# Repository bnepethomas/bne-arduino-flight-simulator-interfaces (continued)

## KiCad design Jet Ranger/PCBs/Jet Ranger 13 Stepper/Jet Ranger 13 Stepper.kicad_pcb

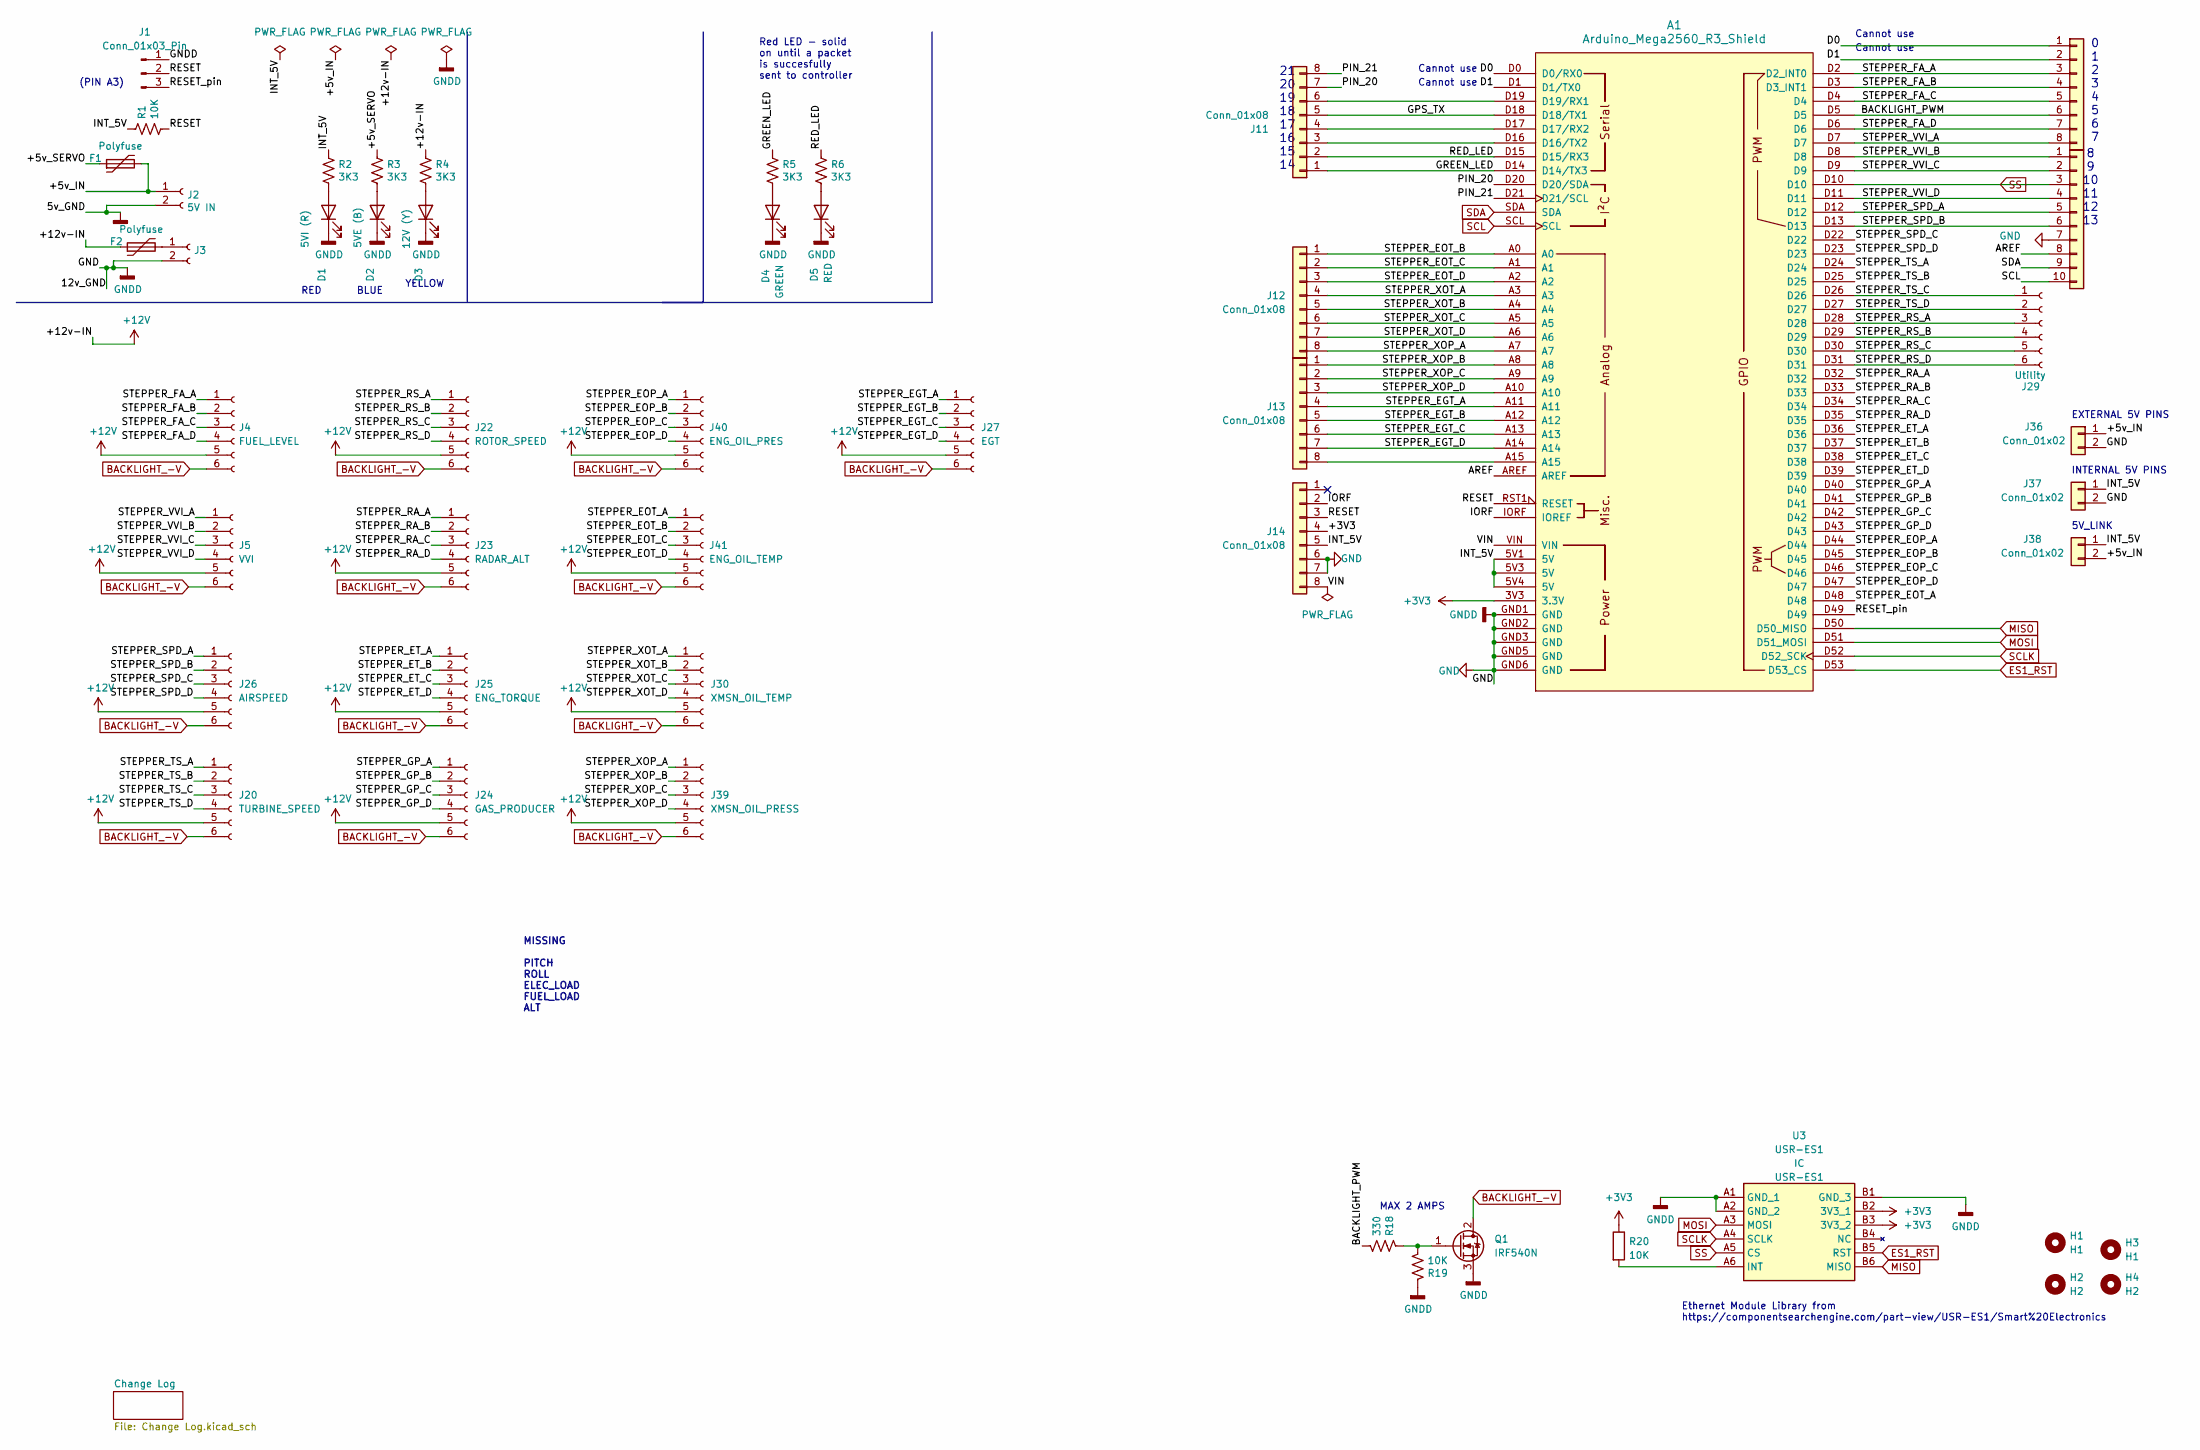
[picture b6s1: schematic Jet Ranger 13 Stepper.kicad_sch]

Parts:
A1: Arduino_Mega2560_R3_Shield
D1: 5VI (R); LED_D3.0mm
D2: 5VE (B); LED_D3.0mm
D3: 12V (Y); LED_D3.0mm
D4: GREEN; LED_D3.0mm
D5: RED; LED_D3.0mm
F1, F2: Polyfuse; Fuse_Littelfuse_395Series
H1, H3: H1; MountingHole_3.2mm_M3
H2, H4: H2; MountingHole_3.2mm_M3
J1: Conn_01x03_Pin; PinHeader_1x03_P2.54mm_Vertical
J2: 5V IN; BarrelJack_Horizontal
J3: STEPPER IN 12-20VDC; BarrelJack_Horizontal
J4: FUEL_LEVEL; Molex_KK-254_AE-6410-06A_1x06_P2.54mm_Vertical
J5: VVI; Molex_KK-254_AE-6410-06A_1x06_P2.54mm_Vertical
J11, J12, J13, J14, J34: Conn_01x08; PinHeader_1x08_P2.54mm_Vertical
J20: TURBINE_SPEED; Molex_KK-254_AE-6410-06A_1x06_P2.54mm_Vertical
J22: ROTOR_SPEED; Molex_KK-254_AE-6410-06A_1x06_P2.54mm_Vertical
J23: RADAR_ALT; Molex_KK-254_AE-6410-06A_1x06_P2.54mm_Vertical
J24: GAS_PRODUCER; Molex_KK-254_AE-6410-06A_1x06_P2.54mm_Vertical
J25: ENG_TORQUE; Molex_KK-254_AE-6410-06A_1x06_P2.54mm_Vertical
J26: AIRSPEED; Molex_KK-254_AE-6410-06A_1x06_P2.54mm_Vertical
J27: EGT; Molex_KK-254_AE-6410-06A_1x06_P2.54mm_Vertical
J29: Utility; PinHeader_1x06_P2.54mm_Vertical
J30: XMSN_OIL_TEMP; Molex_KK-254_AE-6410-06A_1x06_P2.54mm_Vertical
J35: Conn_01x10; PinHeader_1x10_P2.54mm_Vertical
J36, J37, J38: Conn_01x02; PinHeader_1x02_P2.54mm_Vertical
J39: XMSN_OIL_PRESS; Molex_KK-254_AE-6410-06A_1x06_P2.54mm_Vertical
J40: ENG_OIL_PRES; Molex_KK-254_AE-6410-06A_1x06_P2.54mm_Vertical
J41: ENG_OIL_TEMP; Molex_KK-254_AE-6410-06A_1x06_P2.54mm_Vertical
Q1: IRF540N; TO-220-3_Vertical
R1, R19, R20: 10K; R_Axial_DIN0207_L6.3mm_D2.5mm_P2.54mm_Vertical
R2, R3, R4, R5, R6: 3K3; R_Axial_DIN0207_L6.3mm_D2.5mm_P2.54mm_Vertical
R18: 330; R_Axial_DIN0207_L6.3mm_D2.5mm_P2.54mm_Vertical
U3: USR-ES1; USRES1; Manufacturer_Part_Number USR-ES1

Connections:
+3V3: A1.3V3 (3.3V), J14.4, R20.1, U3.B2 (3V3_1), U3.B3 (3V3_2)
+12V: F2.1, J4.5, J5.5, J20.5, J22.5, J23.5, J24.5, J25.5, J26.5, J27.5, J30.5, J39.5, J40.5, J41.5, R4.1
/+5v_IN: F1.2, J2.1, J36.1, J38.2
/+5v_SERVO: F1.1, R3.1
/AREF: A1.AREF, J35.8
/BACKLIGHT_PWM: A1.D5, J34.6, R18.2
/D0: A1.D0 (D0/RX0), J34.1
/D1: A1.D1 (D1/TX0), J34.2
/GPS_TX: A1.D18 (D18/TX1), J11.5
/GREEN_LED: A1.D14 (D14/TX3), J11.1, R5.1
/INT_5V: A1.5V1 (5V), A1.5V3 (5V), A1.5V4 (5V), J14.5, J37.1, J38.1, R1.1, R2.1
/IORF: A1.IORF (IOREF), J14.2
/PIN_20: A1.D20 (D20/SDA), J11.7
/PIN_21: A1.D21 (D21/SCL), J11.8
/RED_LED: A1.D15 (D15/RX3), J11.2, R6.1
/RESET: A1.RST1 (RESET), J1.2, J14.3, R1.2
/RESET_pin: A1.D49, J1.3
/STEPPER_EGT_A: A1.A11, J13.4, J27.1
/STEPPER_EGT_B: A1.A12, J13.5, J27.2
/STEPPER_EGT_C: A1.A13, J13.6, J27.3
/STEPPER_EGT_D: A1.A14, J13.7, J27.4
/STEPPER_EOP_A: A1.D44, J40.1
/STEPPER_EOP_B: A1.D45, J40.2
/STEPPER_EOP_C: A1.D46, J40.3
/STEPPER_EOP_D: A1.D47, J40.4
/STEPPER_EOT_A: A1.D48, J41.1
/STEPPER_EOT_B: A1.A0, J12.1, J41.2
/STEPPER_EOT_C: A1.A1, J12.2, J41.3
/STEPPER_EOT_D: A1.A2, J12.3, J41.4
/STEPPER_ET_A: A1.D36, J25.1
/STEPPER_ET_B: A1.D37, J25.2
/STEPPER_ET_C: A1.D38, J25.3
/STEPPER_ET_D: A1.D39, J25.4
/STEPPER_FA_A: A1.D2 (D2_INT0), J4.1, J34.3
/STEPPER_FA_B: A1.D3 (D3_INT1), J4.2, J34.4
/STEPPER_FA_C: A1.D4, J4.3, J34.5
/STEPPER_FA_D: A1.D6, J4.4, J34.7
/STEPPER_GP_A: A1.D40, J24.1
/STEPPER_GP_B: A1.D41, J24.2
/STEPPER_GP_C: A1.D42, J24.3
/STEPPER_GP_D: A1.D43, J24.4
/STEPPER_RA_A: A1.D32, J23.1
/STEPPER_RA_B: A1.D33, J23.2
/STEPPER_RA_C: A1.D34, J23.3
/STEPPER_RA_D: A1.D35, J23.4
/STEPPER_RS_A: A1.D28, J22.1, J29.3
/STEPPER_RS_B: A1.D29, J22.2, J29.4
/STEPPER_RS_C: A1.D30, J22.3, J29.5
/STEPPER_RS_D: A1.D31, J22.4, J29.6
/STEPPER_SPD_A: A1.D12, J26.1, J35.5
/STEPPER_SPD_B: A1.D13, J26.2, J35.6
/STEPPER_SPD_C: A1.D22, J26.3
/STEPPER_SPD_D: A1.D23, J26.4
/STEPPER_TS_A: A1.D24, J20.1
/STEPPER_TS_B: A1.D25, J20.2
/STEPPER_TS_C: A1.D26, J20.3, J29.1
/STEPPER_TS_D: A1.D27, J20.4, J29.2
/STEPPER_VVI_A: A1.D7, J5.1, J34.8
/STEPPER_VVI_B: A1.D8, J5.2, J35.1
/STEPPER_VVI_C: A1.D9, J5.3, J35.2
/STEPPER_VVI_D: A1.D11, J5.4, J35.4
/STEPPER_XOP_A: A1.A7, J12.8, J39.1
/STEPPER_XOP_B: A1.A8, J13.1, J39.2
/STEPPER_XOP_C: A1.A9, J13.2, J39.3
/STEPPER_XOP_D: A1.A10, J13.3, J39.4
/STEPPER_XOT_A: A1.A3, J12.4, J30.1
/STEPPER_XOT_B: A1.A4, J12.5, J30.2
/STEPPER_XOT_C: A1.A5, J12.6, J30.3
/STEPPER_XOT_D: A1.A6, J12.7, J30.4
/VIN: A1.VIN, J14.8
BACKLIGHT_-V: J4.6, J5.6, J20.6, J22.6, J23.6, J24.6, J25.6, J26.6, J27.6, J30.6, J39.6, J40.6, J41.6, Q1.2 (D)
ES1_RST: A1.D53 (D53_CS), U3.B5 (RST)
GND: A1.GND1 (GND), A1.GND2 (GND), A1.GND3 (GND), A1.GND5 (GND), A1.GND6 (GND), D1.1 (K), D2.1 (K), D3.1 (K), D4.1 (K), D5.1 (K), J1.1, J2.2, J3.2, J14.6, J14.7, J35.7, J36.2, J37.2, Q1.3 (S), R19.1, U3.A1 (GND_1), U3.A2 (GND_2), U3.B1 (GND_3)
MISO: A1.D50 (D50_MISO), U3.B6 (MISO)
MOSI: A1.D51 (D51_MOSI), U3.A3 (MOSI)
unnamed: A1.D16 (D16/TX2), J11.3
unnamed: A1.D17 (D17/RX2), J11.4
unnamed: A1.D19 (D19/RX1), J11.6
unnamed: D1.2 (A), R2.2
unnamed: D2.2 (A), R3.2
unnamed: D3.2 (A), R4.2
unnamed: D4.2 (A), R5.2
unnamed: D5.2 (A), R6.2
unnamed: F2.2, J3.1
unnamed: A1.A15, J13.8
unnamed: Q1.1 (G), R18.1, R19.2
unnamed: R20.2, U3.A6 (INT)
SCL: A1.SCL, J35.10
SCLK: A1.D52 (D52_SCK), U3.A4 (SCLK)
SDA: A1.SDA, J35.9
SS: A1.D10, J35.3, U3.A5 (CS)

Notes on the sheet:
YELLOW
MAX 2 AMPS
MISSING PITCH ROLL ELEC_LOAD FUEL_LOAD ALT
BLUE
INTERNAL 5V PINS
Ethernet Module Library from https://componentsearchengine.com/part-view/USR-ES1/Smart%20Electronics
Cannot use
RED
(PIN A3)
0 1 2 3 4 5 6 7
Red LED - solid on until a packet is succesfully sent to controller
5V_LINK
21 20 19 18 17 16 15 14
EXTERNAL 5V PINS
8 9 10 11 12 13

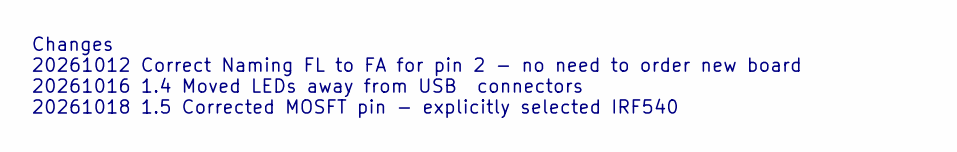
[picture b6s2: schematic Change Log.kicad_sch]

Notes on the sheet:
Changes 20261012 Correct Naming FL to FA for pin 2 - no need to order new board 20261016 1.4 Moved LEDs away from USB connectors 20261018 1.5 Corrected MOSFT pin - explicitly selected IRF540

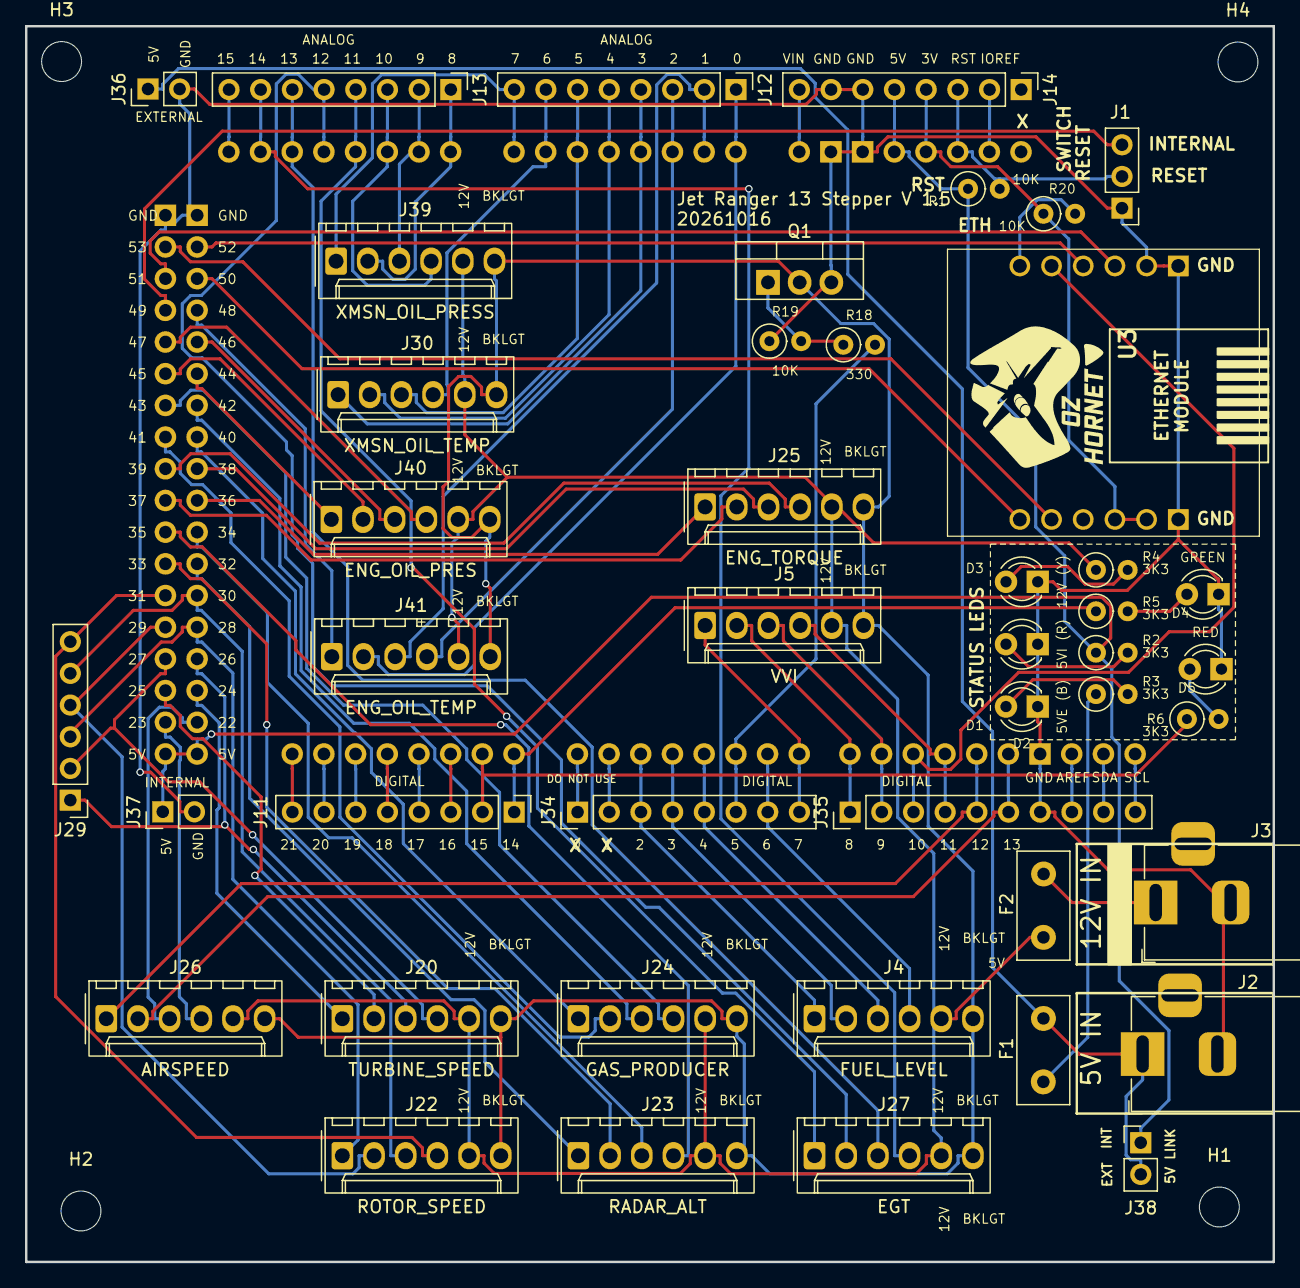
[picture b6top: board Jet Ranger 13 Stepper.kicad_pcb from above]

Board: 2 copper layers, 100.0 x 99.1 mm, 49 parts (0 on the bottom side), 91 nets.

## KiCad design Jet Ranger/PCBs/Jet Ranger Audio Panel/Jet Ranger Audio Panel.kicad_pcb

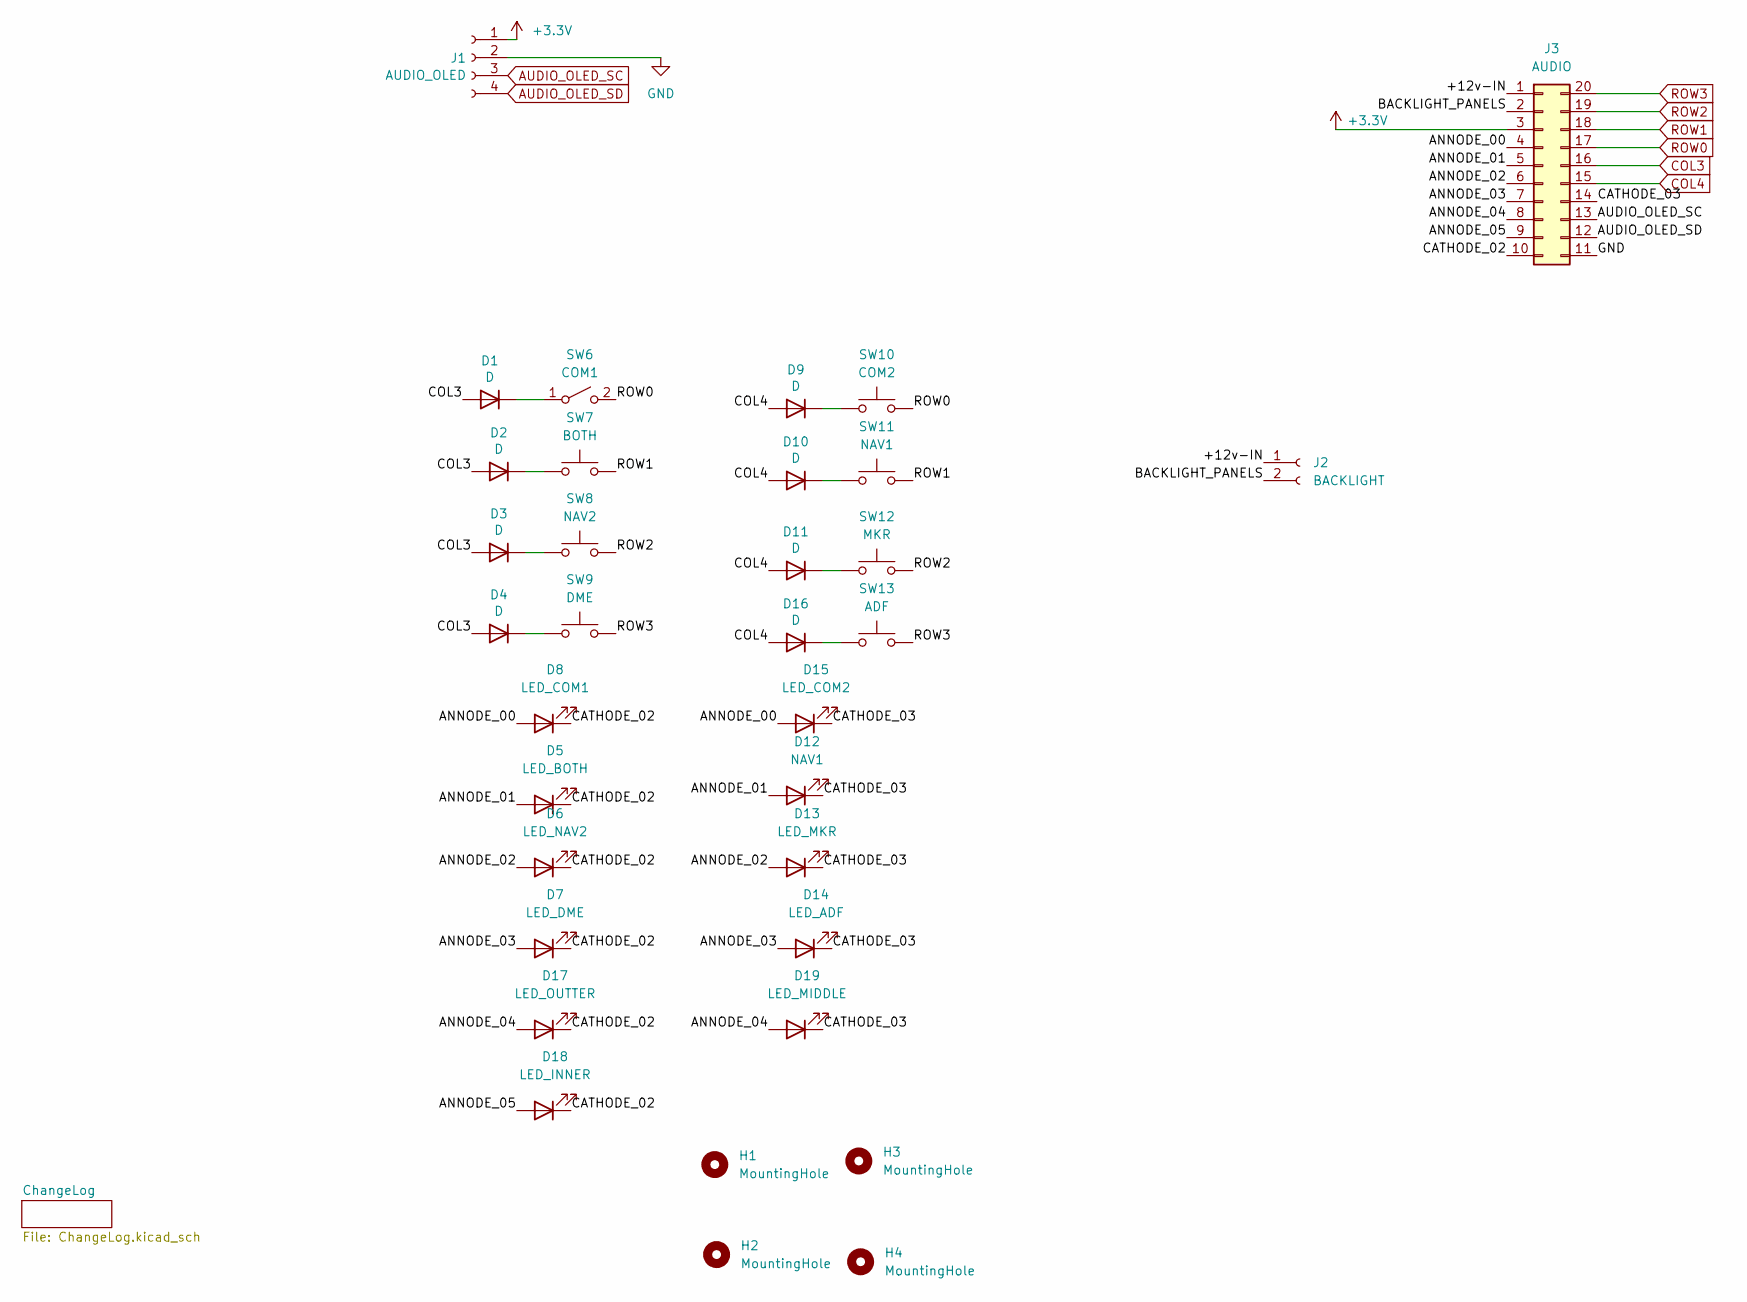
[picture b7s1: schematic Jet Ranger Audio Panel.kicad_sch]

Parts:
D1, D2, D3, D4, D9, D10, D11, D16: D; D_A-405_P7.62mm_Horizontal
D5: LED_BOTH; JST_XH_B2B-XH-A_1x02_P2.50mm_Vertical
D6: LED_NAV2; JST_XH_B2B-XH-A_1x02_P2.50mm_Vertical
D7: LED_DME; JST_XH_B2B-XH-A_1x02_P2.50mm_Vertical
D8: LED_COM1; JST_XH_B2B-XH-A_1x02_P2.50mm_Vertical
D12: NAV1; JST_XH_B2B-XH-A_1x02_P2.50mm_Vertical
D13: LED_MKR; JST_XH_B2B-XH-A_1x02_P2.50mm_Vertical
D14: LED_ADF; JST_XH_B2B-XH-A_1x02_P2.50mm_Vertical
D15: LED_COM2; JST_XH_B2B-XH-A_1x02_P2.50mm_Vertical
D17: LED_OUTTER; JST_XH_B2B-XH-A_1x02_P2.50mm_Vertical
D18: LED_INNER; JST_XH_B2B-XH-A_1x02_P2.50mm_Vertical
D19: LED_MIDDLE; JST_XH_B2B-XH-A_1x02_P2.50mm_Vertical
H1, H2, H3, H4: MountingHole; MountingHole_3.2mm_M3
J1: AUDIO_OLED; JST_XH_B4B-XH-A_1x04_P2.50mm_Vertical
J2: BACKLIGHT; JST_XH_B2B-XH-A_1x02_P2.50mm_Vertical
J3: AUDIO; IDC-Header_2x10_P2.54mm_Vertical
SW6: COM1; JST_XH_B2B-XH-A_1x02_P2.50mm_Vertical
SW7: BOTH; JST_XH_B2B-XH-A_1x02_P2.50mm_Vertical
SW8: NAV2; JST_XH_B2B-XH-A_1x02_P2.50mm_Vertical
SW9: DME; JST_XH_B2B-XH-A_1x02_P2.50mm_Vertical
SW10: COM2; JST_XH_B2B-XH-A_1x02_P2.50mm_Vertical
SW11: NAV1; JST_XH_B2B-XH-A_1x02_P2.50mm_Vertical
SW12: MKR; JST_XH_B2B-XH-A_1x02_P2.50mm_Vertical
SW13: ADF; JST_XH_B2B-XH-A_1x02_P2.50mm_Vertical

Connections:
+3.3V: J1.1, J3.3
/+12v-IN: J2.1, J3.1
/ANNODE_00: D8.1 (A), D15.1 (A), J3.4
/ANNODE_01: D5.1 (A), D12.1 (A), J3.5
/ANNODE_02: D6.1 (A), D13.1 (A), J3.6
/ANNODE_03: D7.1 (A), D14.1 (A), J3.7
/ANNODE_04: D17.1 (A), D19.1 (A), J3.8
/ANNODE_05: D18.1 (A), J3.9
/BACKLIGHT_PANELS: J2.2, J3.2
/CATHODE_02: D5.2 (K), D6.2 (K), D7.2 (K), D8.2 (K), D17.2 (K), D18.2 (K), J3.10
/CATHODE_03: D12.2 (K), D13.2 (K), D14.2 (K), D15.2 (K), D19.2 (K), J3.14
AUDIO_OLED_SC: J1.3, J3.13
AUDIO_OLED_SD: J1.4, J3.12
COL3: D1.2 (A), D2.2 (A), D3.2 (A), D4.2 (A), J3.16
COL4: D9.2 (A), D10.2 (A), D11.2 (A), D16.2 (A), J3.15
GND: J1.2, J3.11
unnamed: D1.1 (K), SW6.1 (A)
unnamed: D2.1 (K), SW7.1
unnamed: D3.1 (K), SW8.1
unnamed: D4.1 (K), SW9.1
unnamed: D9.1 (K), SW10.1
unnamed: D10.1 (K), SW11.1
unnamed: D11.1 (K), SW12.1
unnamed: D16.1 (K), SW13.1
ROW0: J3.17, SW6.2 (B), SW10.2
ROW1: J3.18, SW7.2, SW11.2
ROW2: J3.19, SW8.2, SW12.2
ROW3: J3.20, SW9.2, SW13.2

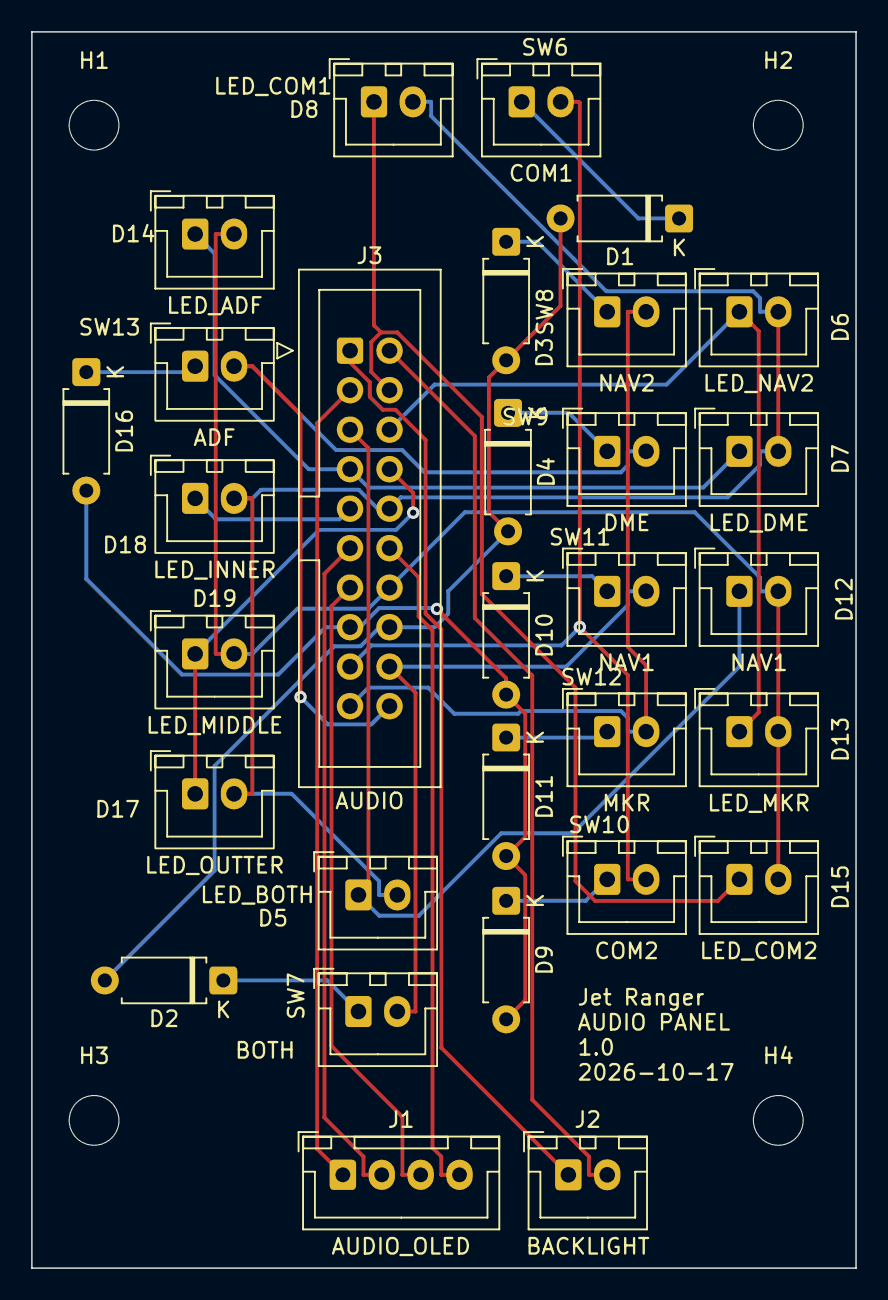
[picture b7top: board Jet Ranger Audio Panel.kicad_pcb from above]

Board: 2 copper layers, 53.0 x 79.5 mm, 34 parts (0 on the bottom side), 28 nets.

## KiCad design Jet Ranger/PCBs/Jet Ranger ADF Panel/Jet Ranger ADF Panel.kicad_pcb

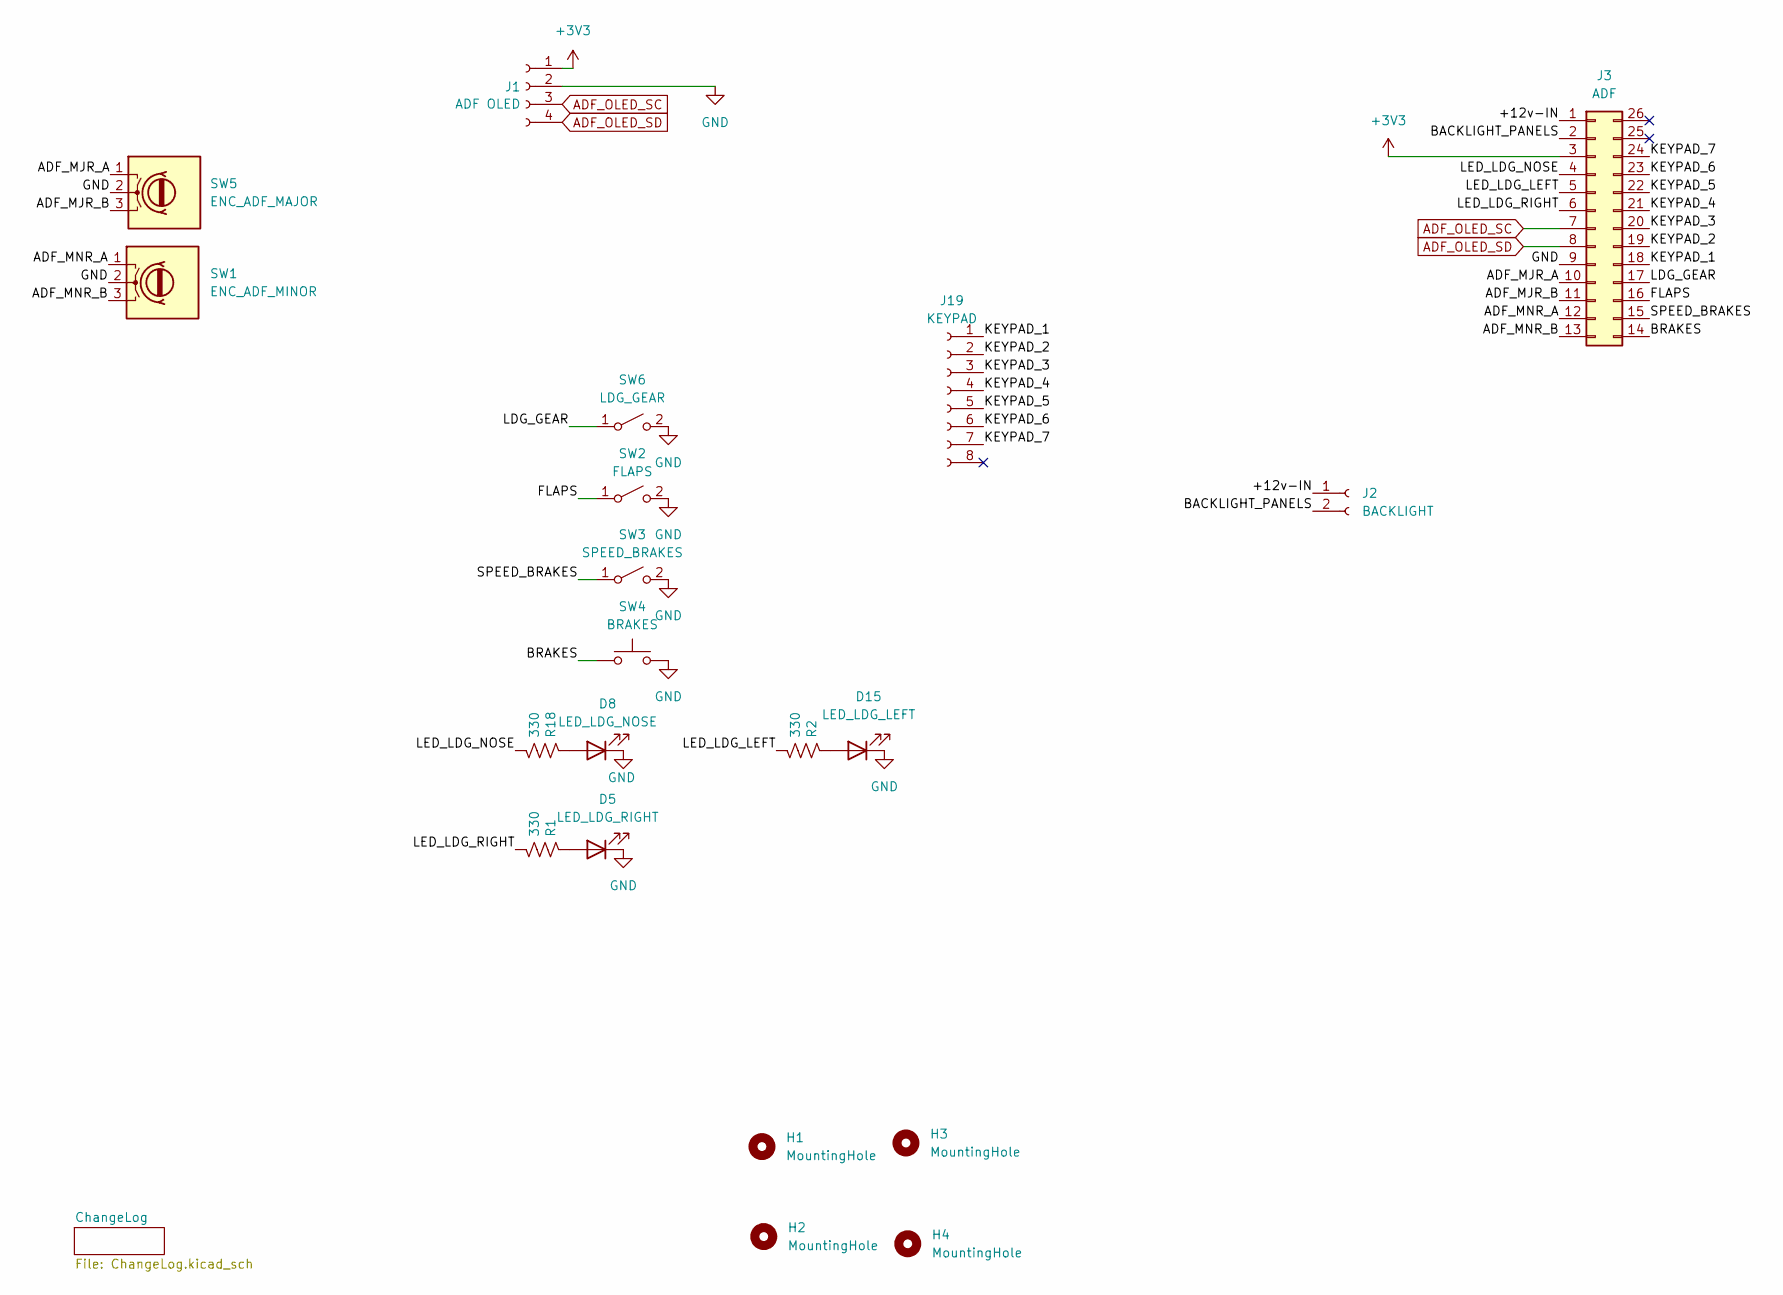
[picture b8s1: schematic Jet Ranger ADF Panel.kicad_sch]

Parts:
D5: LED_LDG_RIGHT; JST_XH_B2B-XH-A_1x02_P2.50mm_Vertical
D8: LED_LDG_NOSE; JST_XH_B2B-XH-A_1x02_P2.50mm_Vertical
D15: LED_LDG_LEFT; JST_XH_B2B-XH-A_1x02_P2.50mm_Vertical
H1, H2, H3, H4: MountingHole; MountingHole_3.2mm_M3
J1: ADF OLED; JST_XH_B4B-XH-A_1x04_P2.50mm_Vertical
J2: BACKLIGHT; JST_XH_B2B-XH-A_1x02_P2.50mm_Vertical
J3: ADF; IDC-Header_2x13_P2.54mm_Vertical
J19: KEYPAD; Molex_KK-254_AE-6410-08A_1x08_P2.54mm_Vertical
R1, R2, R18: 330; R_Axial_DIN0207_L6.3mm_D2.5mm_P2.54mm_Vertical
SW1: ENC_ADF_MINOR; JST_XH_B3B-XH-A_1x03_P2.50mm_Vertical
SW2: FLAPS; JST_XH_B2B-XH-A_1x02_P2.50mm_Vertical
SW3: SPEED_BRAKES; JST_XH_B2B-XH-A_1x02_P2.50mm_Vertical
SW4: BRAKES; JST_XH_B2B-XH-A_1x02_P2.50mm_Vertical
SW5: ENC_ADF_MAJOR; JST_XH_B3B-XH-A_1x03_P2.50mm_Vertical
SW6: LDG_GEAR; JST_XH_B2B-XH-A_1x02_P2.50mm_Vertical

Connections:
+3V3: J1.1, J3.3
/+12v-IN: J2.1, J3.1
/ADF_MJR_A: J3.10, SW5.1 (A)
/ADF_MJR_B: J3.11, SW5.3 (B)
/ADF_MNR_A: J3.12, SW1.1 (A)
/ADF_MNR_B: J3.13, SW1.3 (B)
/BACKLIGHT_PANELS: J2.2, J3.2
/BRAKES: J3.14, SW4.1
/FLAPS: J3.16, SW2.1 (A)
/KEYPAD_1: J3.18, J19.1
/KEYPAD_2: J3.19, J19.2
/KEYPAD_3: J3.20, J19.3
/KEYPAD_4: J3.21, J19.4
/KEYPAD_5: J3.22, J19.5
/KEYPAD_6: J3.23, J19.6
/KEYPAD_7: J3.24, J19.7
/LDG_GEAR: J3.17, SW6.1 (A)
/LED_LDG_LEFT: J3.5, R2.2
/LED_LDG_NOSE: J3.4, R18.2
/LED_LDG_RIGHT: J3.6, R1.2
/SPEED_BRAKES: J3.15, SW3.1 (A)
ADF_OLED_SC: J1.3, J3.7
ADF_OLED_SD: J1.4, J3.8
GND: D5.2 (K), D8.2 (K), D15.2 (K), J1.2, J3.9, SW1.2 (C), SW2.2 (B), SW3.2 (B), SW4.2, SW5.2 (C), SW6.2 (B)
unnamed: D5.1 (A), R1.1
unnamed: D8.1 (A), R18.1
unnamed: D15.1 (A), R2.1

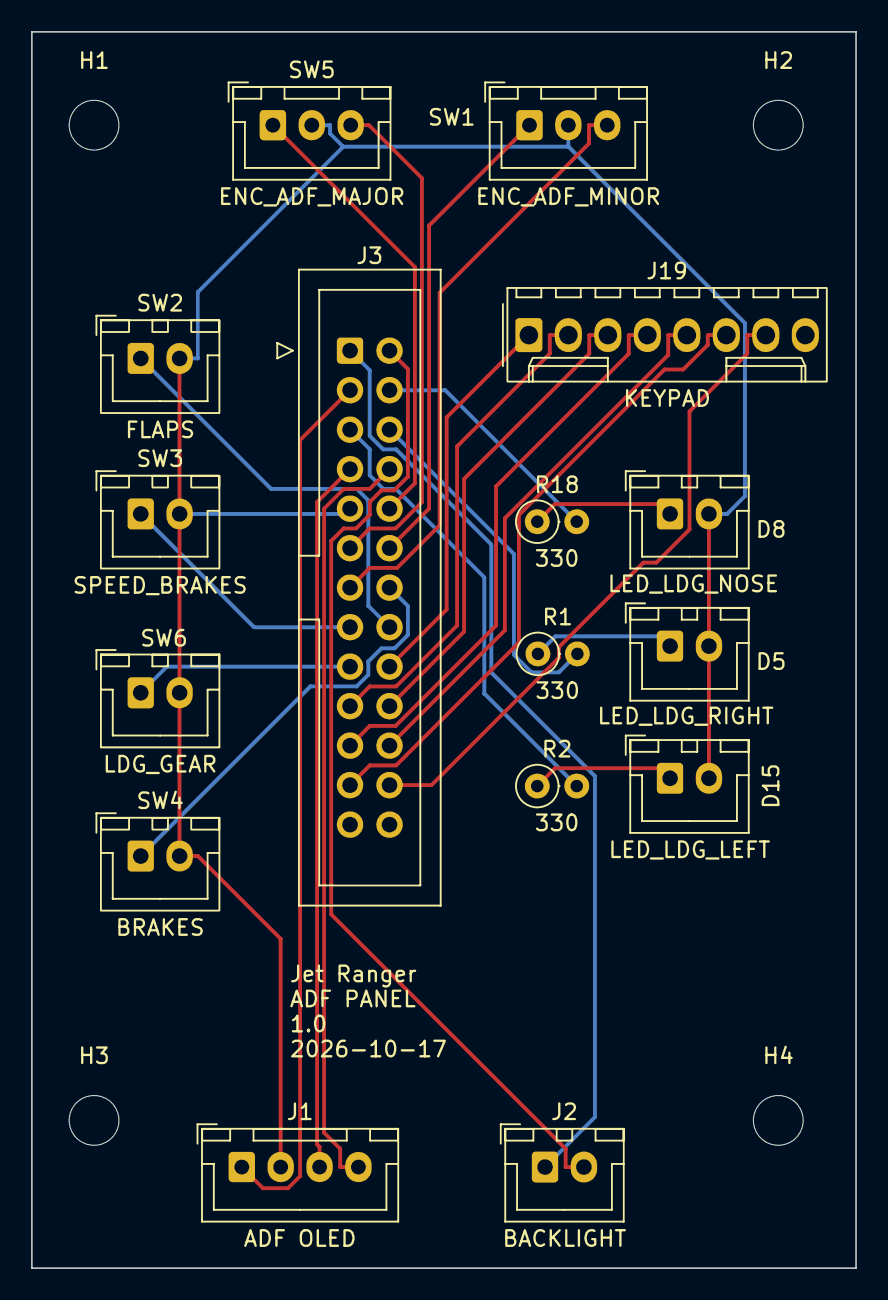
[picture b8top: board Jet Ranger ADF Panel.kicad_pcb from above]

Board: 2 copper layers, 53.0 x 79.5 mm, 20 parts (0 on the bottom side), 27 nets.

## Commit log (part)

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2026-01-26 c# most of Jet Ranger base values set - need to work on radios
2026-01-27 comm is working
2026-01-28 Due Prodcution Controller
2026-01-28 jet ranger
2026-01-28 due pcb update
2026-01-29 due controller
2026-01-29 controller
2026-01-29 DUE Prod
2026-01-30 encoder
2026-01-30 Radio controller working with Mega
2026-01-31 displays updating correctly
2026-02-01 added UDP listener
2026-02-01 before .net migration
2026-02-01 Arduin Now Sending COM1 Stand by to MSFS
2026-02-01 PCB UPDATE
2026-02-02 radio controller push button framework
2026-02-03 progressing on swap
2026-02-03 comm swap working
2026-02-03 comm work
2026-02-06 Handling UDP from MSFS
2026-02-06 COM1 frequencies now working
2026-02-06 comm1 and 2
2026-02-07 timing adjusted
2026-02-07 battery switch no longer working
2026-02-07 Battery Monitoring working bt Avionics isn't
    After tinkeirng with Event Var and perhaps a logic mistake in event handling
2026-02-07 Main Bus working - unsure why Avionics bus isn't working
    Need to looked at BCD encoding for 5KHz radio spacing
2026-02-07 Voltages now nderstood
    To do Set Frequency using string
2026-02-07 Working with needing BCD for Radios
2026-02-07 Radios working and added Monitoring Applicaiotn
2026-02-08 comms workings frequency non-BCD
    Unable to set Garmin 1000 buttons - need to research if FSUIPC with WASM may be able to solve
2026-02-08 C# side of front panel largely done
2026-02-08 power pcbs with aliexpress connector
2026-02-08 updating Servos
2026-02-09 Indicators
2026-02-10 servo range build out
2026-02-11 gauges
2026-02-12 Servo
    Torque is jittering after attach
2026-02-12 Update JET_RANGER_SERVO_CONTROLLER.ino
    Fixed Servo Jitter be checking for incoming packets every so many mS instead of everytime through the loop
2026-02-13 Servo Test Framework
2026-02-14 Servo Tuner Operational
2026-02-14 Servo work
2026-02-14 Servos
2026-02-14 framework may be working
2026-02-14 Torque is now operational
    Whoot
2026-02-14 working on airspeed
2026-02-15 new c# Project target c# 10
2026-02-15 closed
2026-02-15 airspeed working
2026-02-15 Rotor and Engine RPM
2026-02-15 Fuel Qantity
2026-02-15 Fuel Gauge
2026-02-15 VSI Gauge
2026-02-15 Working on Eng Oil Temp and Pressure gauges not moving
2026-02-15 working on XMSN and need to complete Eng and XSMN in sender
2026-02-16 Bank and Pitch to do
2026-02-16 Roll anbd Bank compelte
    to do
    build new PCB
    Elec load, Fuel Loan Gas Producer Radar Alt
2026-02-20 Fuel & Elec Load, Gas P start dev
2026-02-20 TUNER AND MEGA COMPLETE - NEED TO GET VALUES FROM MSFS
2026-02-21 light test routine ok - now need to develop logic
2026-02-21 working on ITT values
2026-02-21 to fix pitch and roll
2026-02-21 still have a few gauges to align and perhaps add calls to
2026-02-21 Engine out and Rotor Low Warnings now ok
    Needed to compare string not numeric
2026-02-21 troubleshooting gauges
    discovered transmission is deprecated in SimConnect
2026-02-24 comm1 working comm2 and nav1 known bad
2026-02-26 COMMNAV
2026-02-28 rolling minor digit
2026-03-01 Update JET_RANGER_RADIO_CONTROLLER.ino
    Nav Minors need to fix rolling over 990
2026-03-02 Update JET_RANGER_RADIO_CONTROLLER.ino
    Minor Encoders now rolling - todo SimConnect interface for Com2 and Nav
2026-04-26 CrossPlatform First cut
2026-04-26 Cross Platform - compiled and executed
2026-05-04 multi-platform
2026-05-09 retired old input controller
2026-05-10 shorten A
2026-05-10 short2
2026-05-10 shorten3
2026-05-10 shorten4
2026-05-10 shorten5
2026-05-10 Hornet Health Monitor
2026-05-10 Create insert for keepalive
2026-05-11 keepalive added to current boards
2026-05-13 Health Monitor
2026-05-15 MHornetHealthMonitor
2026-05-15 health
2026-05-16 sim control
2026-05-16 right sim control
2026-05-17 Mostly working
2026-05-17 compass
2026-05-18 simcontrol
2026-05-22 left and right lighting
2026-05-24 potentiometer update
2026-05-31 keystrokes and lua
2026-06-07 Backlighting
2026-06-20 New debounce architecture
2026-06-20 new debounced cleanup
    was out of memory on UIP
2026-06-27 737 Displays Configuration
2026-06-27 throttle
2026-06-27 737 Doc updaate
